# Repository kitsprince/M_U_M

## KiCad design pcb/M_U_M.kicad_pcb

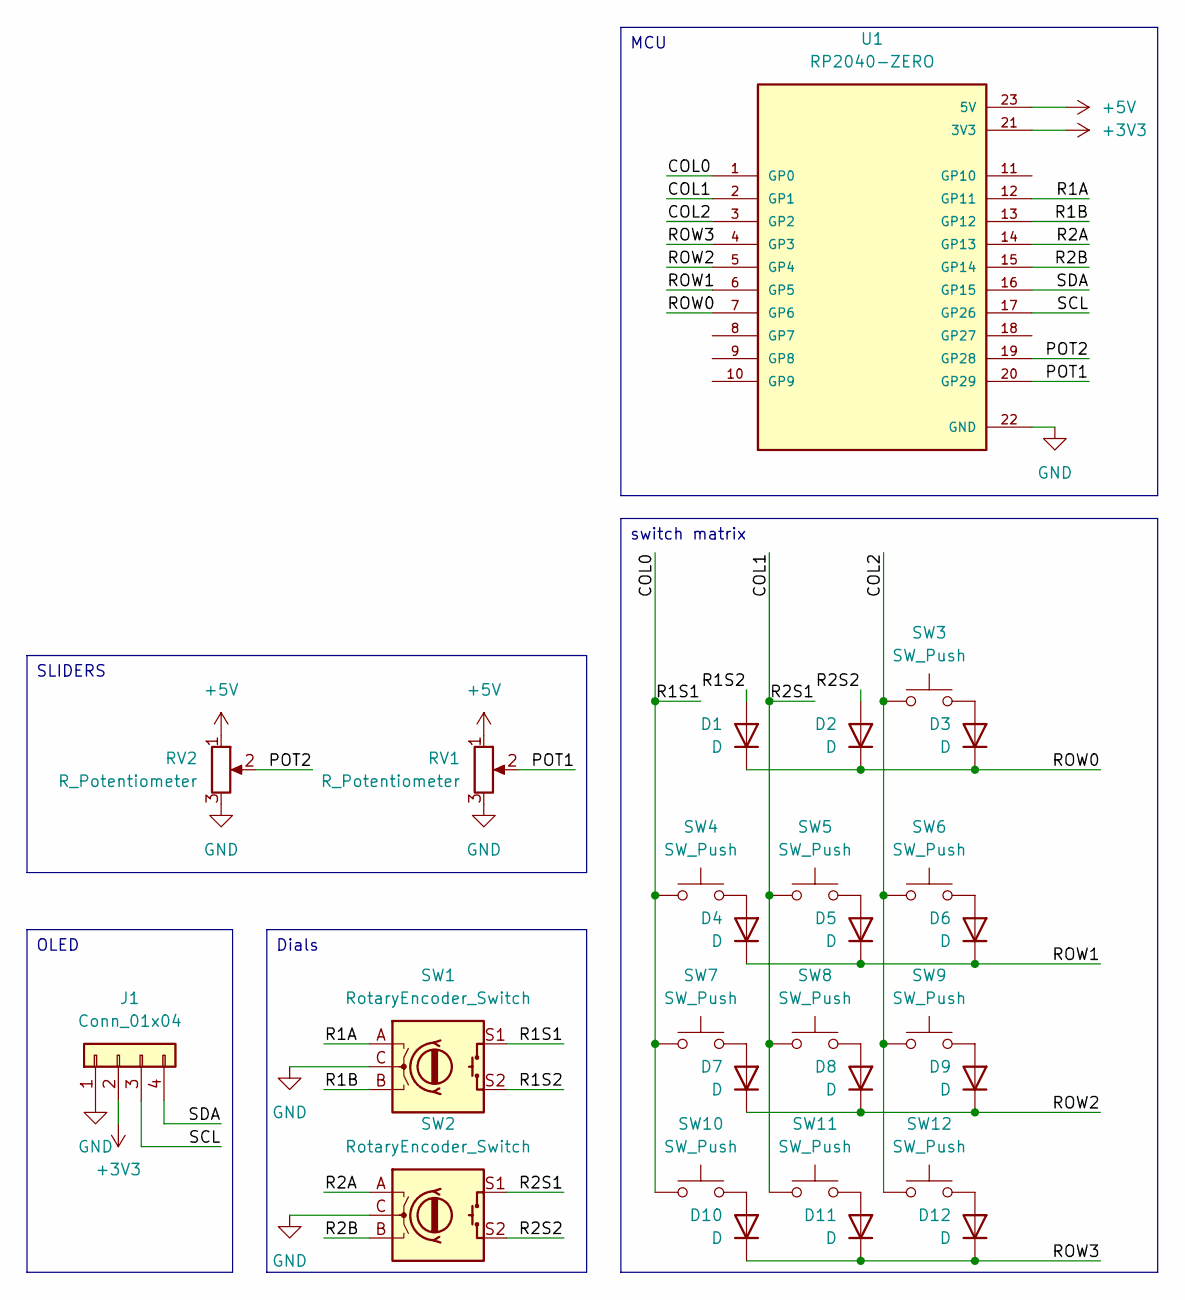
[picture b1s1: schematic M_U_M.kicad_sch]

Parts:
D1, D2, D3, D4, D5, D6, D7, D8, D9, D10, D11, D12: D; D_DO-35_SOD27_P7.62mm_Horizontal
J1: Conn_01x04; PinSocket_1x04_P2.54mm_Vertical
RV1, RV2: R_Potentiometer; Potentiometer_Bourns_PTA6043_Single_Slide
SW1, SW2: RotaryEncoder_Switch; RotaryEncoder_Alps_EC11E-Switch_Vertical_H20mm
SW3, SW4, SW5, SW6, SW7, SW8, SW9, SW10, SW11, SW12: SW_Push; SW_Cherry_MX_1.00u_PCB
U1: RP2040-ZERO; MODULE_RP2040-ZERO; PARTREV NA

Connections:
+3V3: J1.2, U1.21 (3V3)
+5V: RV1.1, RV2.1, U1.23 (5V)
/COL0: SW1.S1, SW4.1, SW7.1, SW10.1, U1.1 (GP0)
/COL1: SW2.S1, SW5.1, SW8.1, SW11.1, U1.2 (GP1)
/COL2: SW3.1, SW6.1, SW9.1, SW12.1, U1.3 (GP2)
/POT1: RV1.2, U1.20 (GP29)
/POT2: RV2.2, U1.19 (GP28)
/R1A: SW1.A, U1.12 (GP11)
/R1B: SW1.B, U1.13 (GP12)
/R1S2: D1.2 (A), SW1.S2
/R2A: SW2.A, U1.14 (GP13)
/R2B: SW2.B, U1.15 (GP14)
/R2S2: D2.2 (A), SW2.S2
/ROW0: D1.1 (K), D2.1 (K), D3.1 (K), U1.7 (GP6)
/ROW1: D4.1 (K), D5.1 (K), D6.1 (K), U1.6 (GP5)
/ROW2: D7.1 (K), D8.1 (K), D9.1 (K), U1.5 (GP4)
/ROW3: D10.1 (K), D11.1 (K), D12.1 (K), U1.4 (GP3)
/SCL: J1.3, U1.17 (GP26)
/SDA: J1.4, U1.16 (GP15)
GND: J1.1, RV1.3, RV2.3, SW1.C, SW2.C, U1.22 (GND)
unnamed: D3.2 (A), SW3.2
unnamed: D4.2 (A), SW4.2
unnamed: D5.2 (A), SW5.2
unnamed: D6.2 (A), SW6.2
unnamed: D7.2 (A), SW7.2
unnamed: D8.2 (A), SW8.2
unnamed: D9.2 (A), SW9.2
unnamed: D10.2 (A), SW10.2
unnamed: D11.2 (A), SW11.2
unnamed: D12.2 (A), SW12.2

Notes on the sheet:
OLED
SLIDERS
switch matrix
MCU
Dials

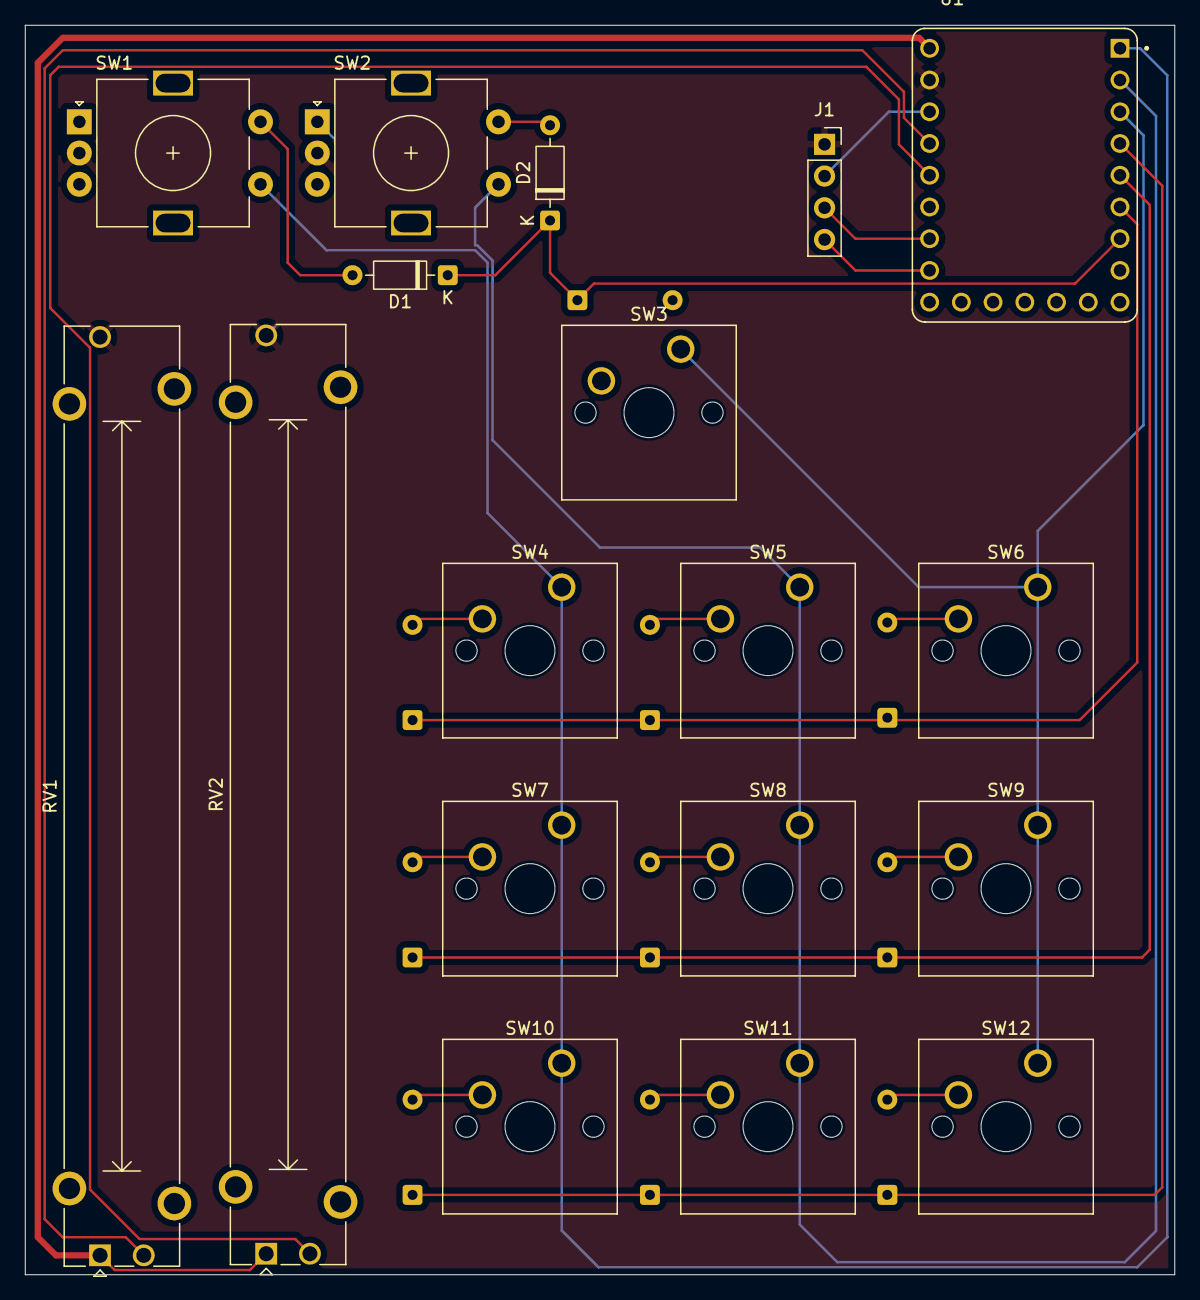
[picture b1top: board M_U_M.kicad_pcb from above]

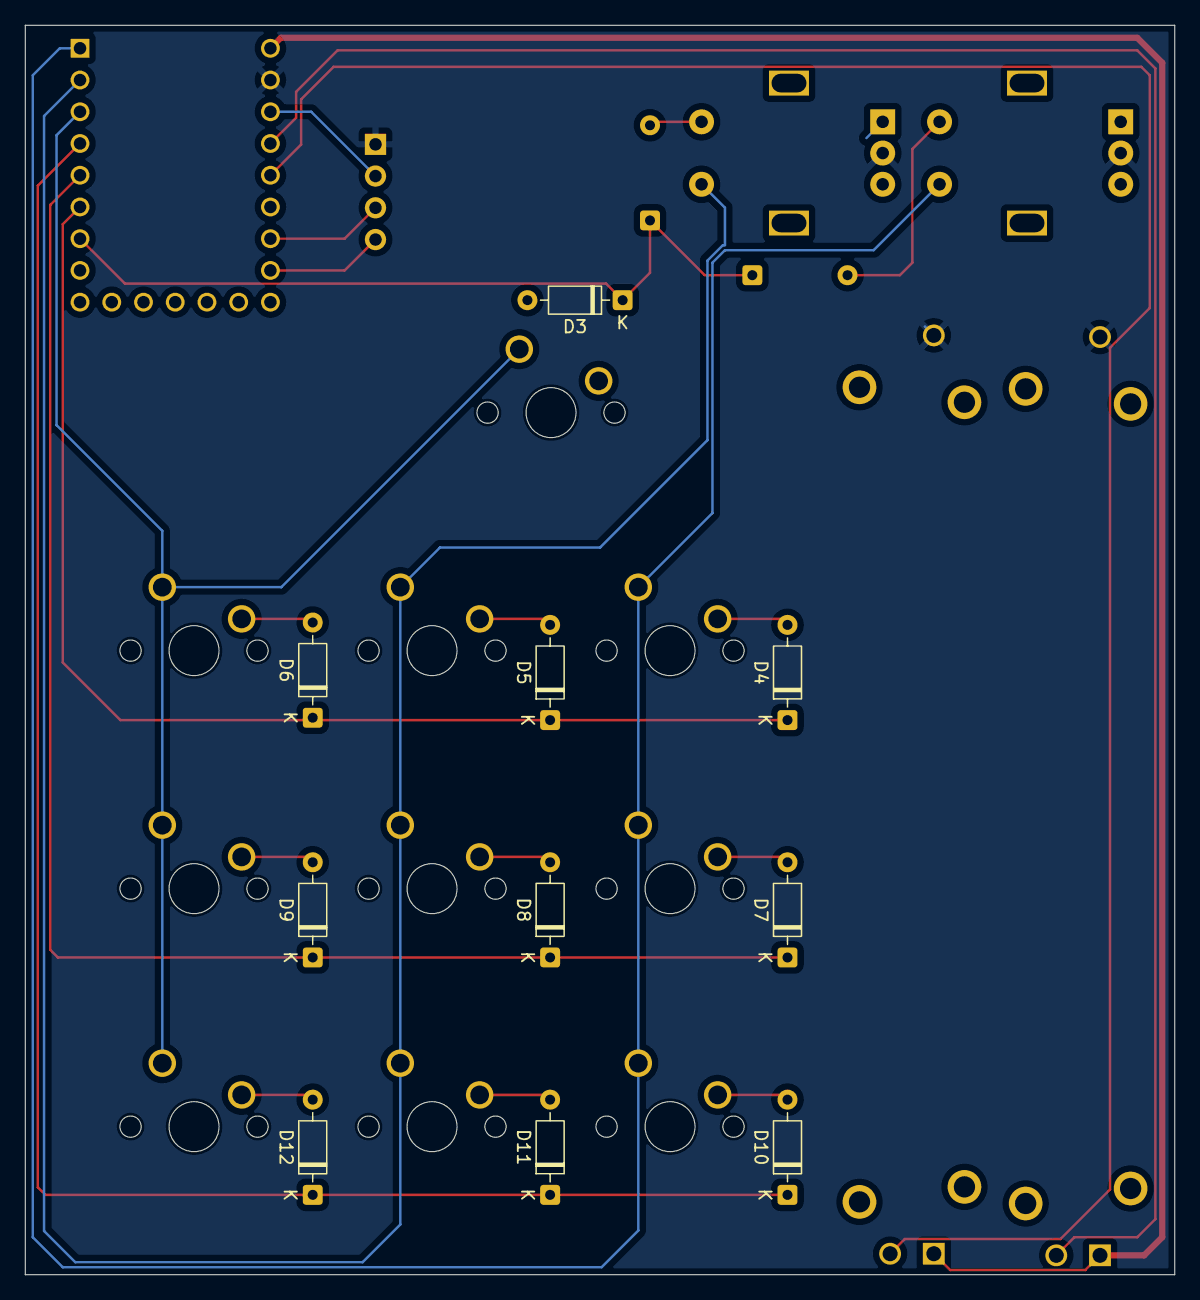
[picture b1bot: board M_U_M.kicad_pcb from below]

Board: 2 copper layers, 92.0 x 100.0 mm, 28 parts (10 on the bottom side), 30 nets.

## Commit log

2025-10-19 we updated and routed
2025-10-19 added ground fill
